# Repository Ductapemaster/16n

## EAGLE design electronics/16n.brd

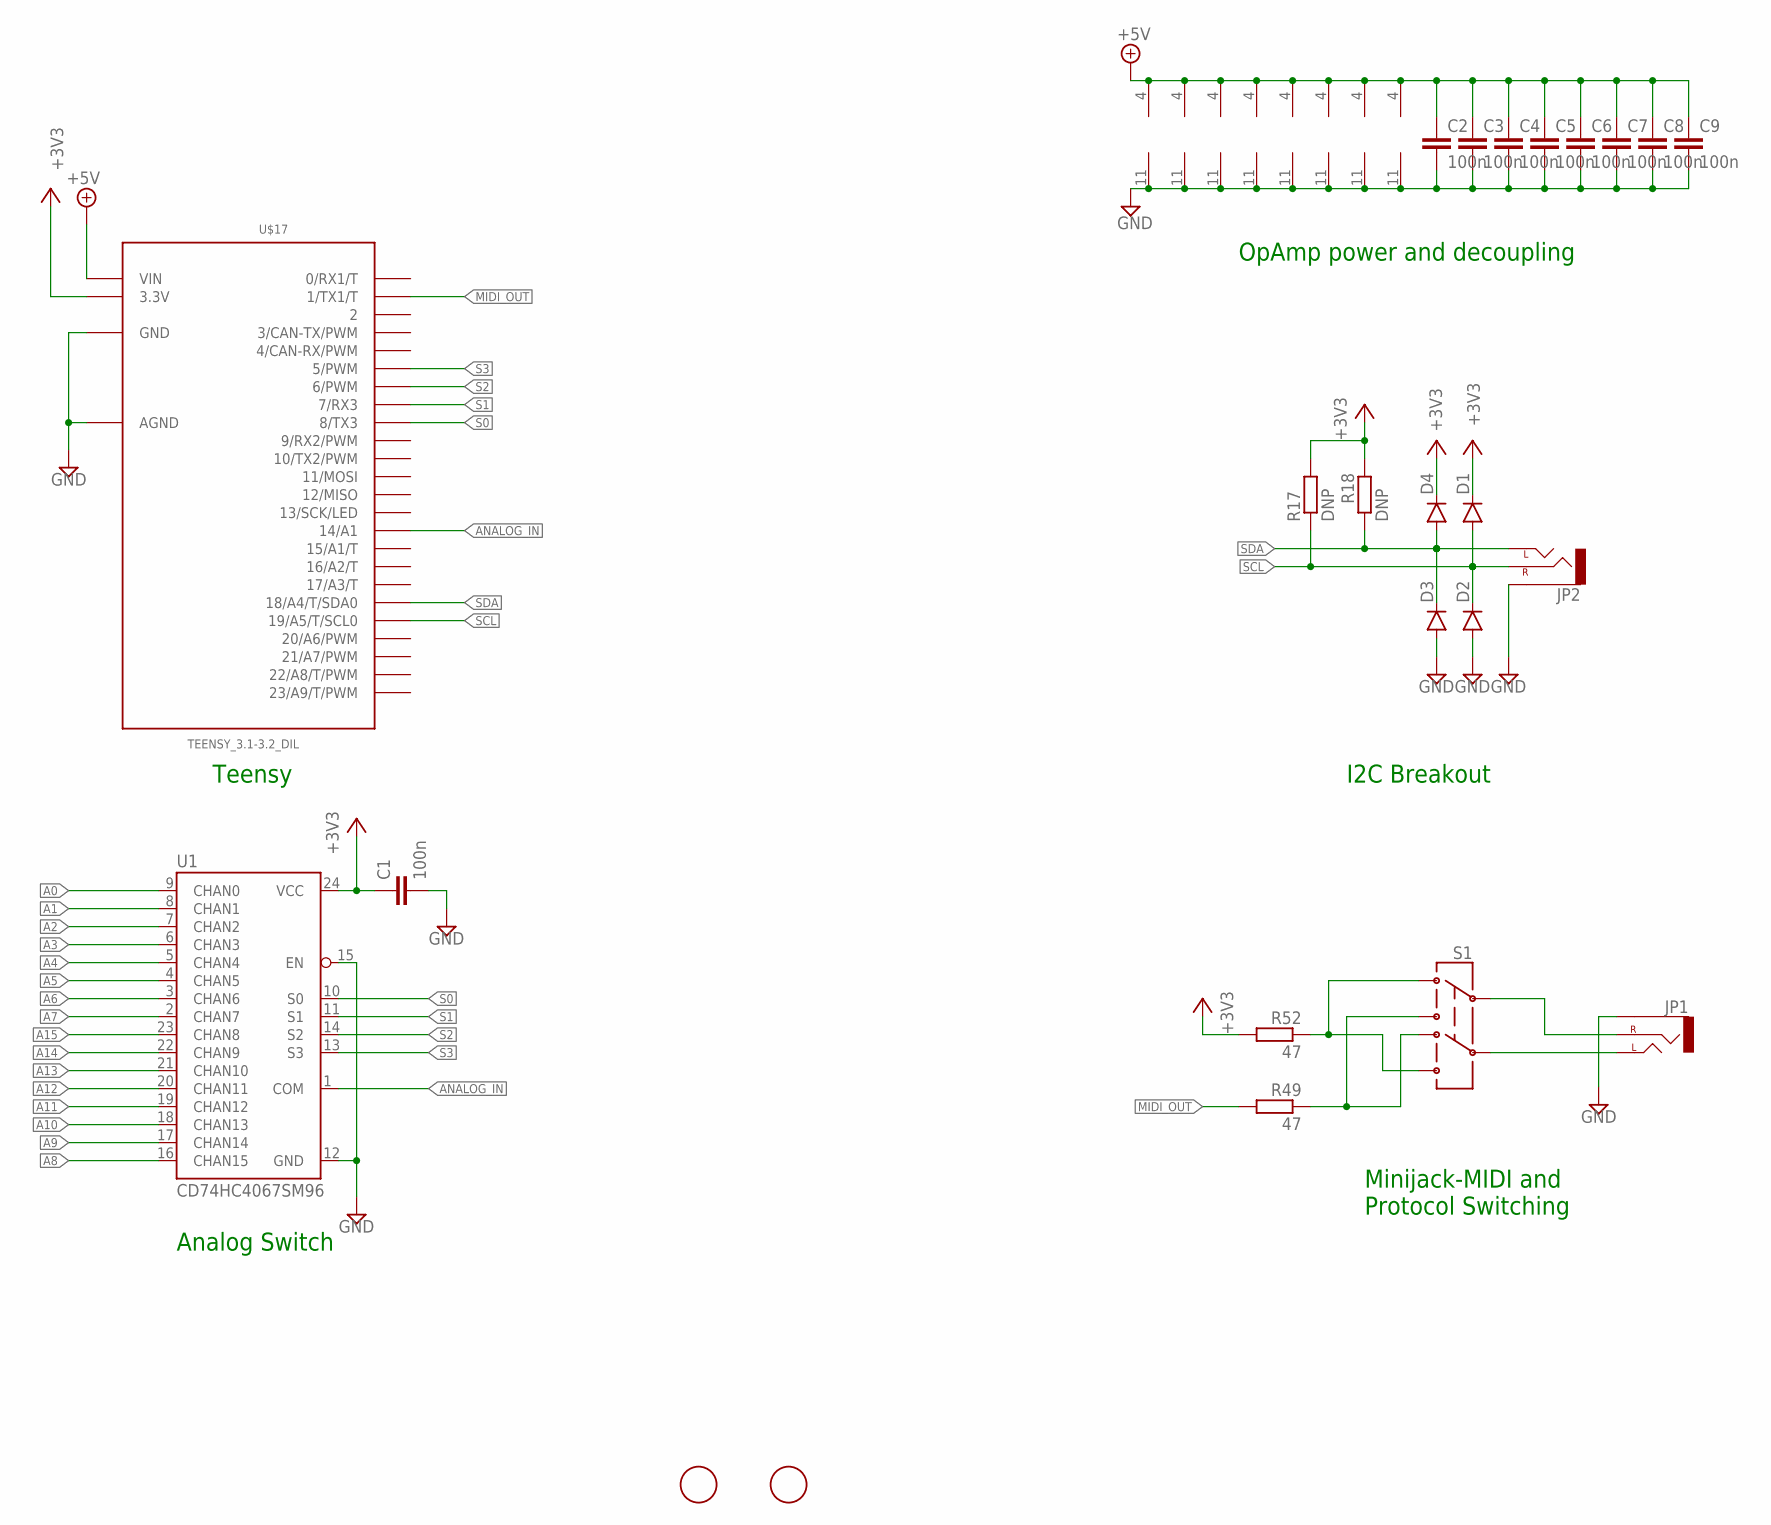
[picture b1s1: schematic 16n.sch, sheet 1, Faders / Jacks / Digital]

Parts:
C1, C2, C3, C4, C5, C6, C7, C8, C9: 100n; C0805
D1, D2, D3, D4: DIODESOD123; SOD-123
FID1, FID2: FIDUCIAL; FIDUCIAL_1MM
JP1, JP2: AUDIO-JACKPTH; AUDIO-JACK
R17, R18: DNP; R0805
R49, R52: 47; R0805
S1: SWITCH-DPDTEG2211; EG2211
U1: CD74HC4067SM96; SOIC127P1030X265-24
U2, U3, U4, U5, U6, U7, U8: MCP6004_SMD; SO14
U9: MCP6004; SO14
U$17: TEENSY_3.1-3.2_DIL; TEENSY_3.0-3.2&LC_DIL

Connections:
+3V3: C1.1, D1.C, D4.C, R17.2, R18.2, R52.2, U1.24 (VCC), U$17.3.3V
+5V: C2.1, C3.1, C4.1, C5.1, C6.1, C7.1, C8.1, C9.1, U2.4 (V+), U3.4 (V+), U4.4 (V+), U5.4 (V+), U6.4 (V+), U7.4 (V+), U8.4 (V+), U9.4 (V+), U$17.VIN; also elsewhere on the board
A0: U1.9 (CHAN0); also elsewhere on the board
A1: U1.8 (CHAN1); also elsewhere on the board
A2: U1.7 (CHAN2); also elsewhere on the board
A3: U1.6 (CHAN3); also elsewhere on the board
A4: U1.5 (CHAN4); also elsewhere on the board
A5: U1.4 (CHAN5); also elsewhere on the board
A6: U1.3 (CHAN6); also elsewhere on the board
A7: U1.2 (CHAN7); also elsewhere on the board
A8: U1.16 (CHAN15); also elsewhere on the board
A9: U1.17 (CHAN14); also elsewhere on the board
A10: U1.18 (CHAN13); also elsewhere on the board
A11: U1.19 (CHAN12); also elsewhere on the board
A12: U1.20 (CHAN11); also elsewhere on the board
A13: U1.21 (CHAN10); also elsewhere on the board
A14: U1.22 (CHAN9); also elsewhere on the board
A15: U1.23 (CHAN8); also elsewhere on the board
ANALOG_IN: U1.1 (COM), U$17.14/A0 (14/A1)
GND: C1.2, C2.2, C3.2, C4.2, C5.2, C6.2, C7.2, C8.2, C9.2, D2.A, D3.A, JP1.SLEEVE, JP2.SLEEVE, U1.12 (GND), U1.15 (EN), U2.11 (V-), U3.11 (V-), U4.11 (V-), U5.11 (V-), U6.11 (V-), U7.11 (V-), U8.11 (V-), U9.11 (V-), U$17.AGND, U$17.GND; also elsewhere on the board
MIDI_OUT: R49.2, U$17.1 (1/TX1/T)
unnamed: JP1.TIP (LEFT), S1.P2 (5)
unnamed: JP1.RING (RIGHT), S1.P1 (2)
unnamed: R49.1, S1.P1-TB (3), S1.P2-TA (4)
unnamed: R52.1, S1.P1-TA (1), S1.P2-TB (6)
S0: U1.10 (S0), U$17.8 (8/TX3)
S1: U1.11 (S1), U$17.7 (7/RX3)
S2: U1.14 (S2), U$17.6 (6/PWM)
S3: U1.13 (S3), U$17.5 (5/PWM)
SCL: D1.A, D2.C, JP2.RING (RIGHT), R17.1, U$17.19/A5 (19/A5/T/SCL0)
SDA: D3.C, D4.A, JP2.TIP (LEFT), R18.1, U$17.18/A4 (18/A4/T/SDA0)

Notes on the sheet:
Teensy
Minijack-MIDI and Protocol Switching
I2C Breakout
OpAmp power and decoupling
Analog Switch

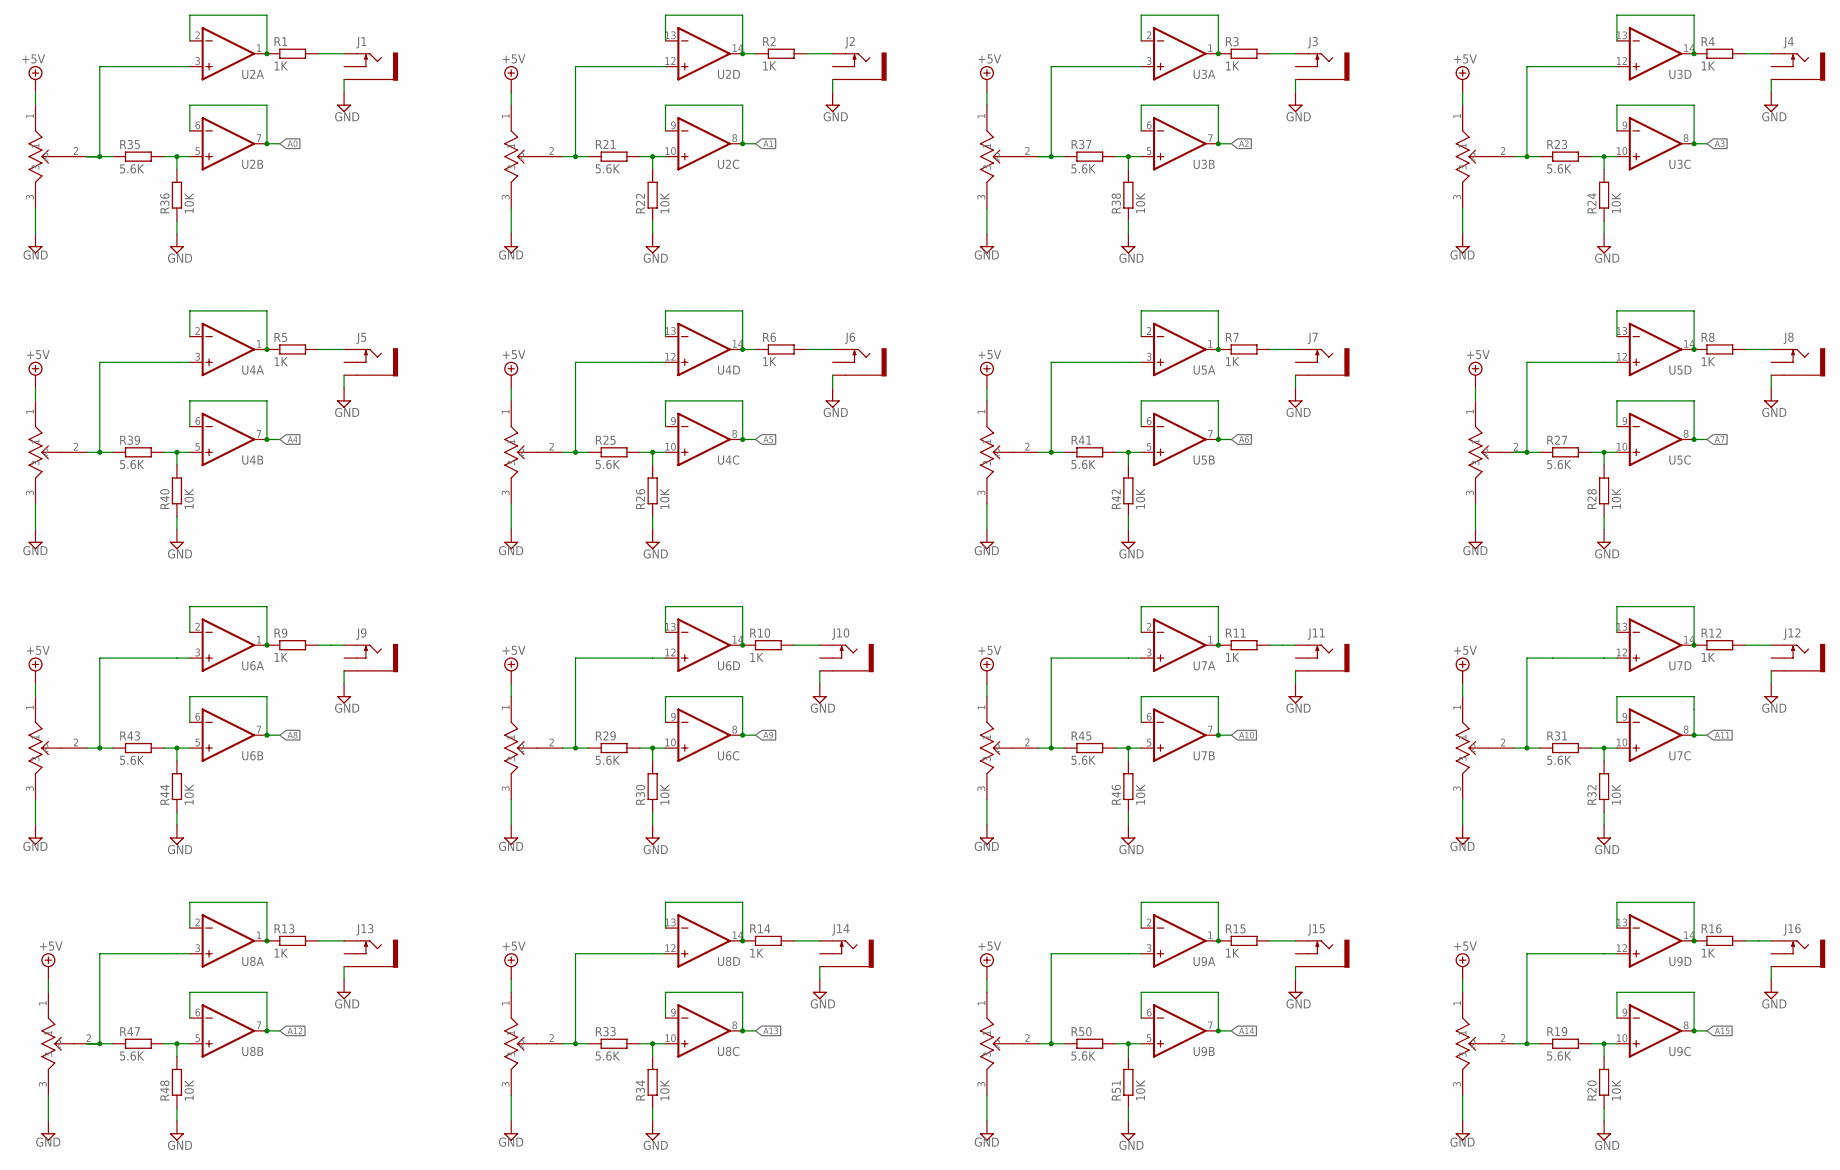
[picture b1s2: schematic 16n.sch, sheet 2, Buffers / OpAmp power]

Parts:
J1, J2, J3, J4, J5, J6, J7, J8, J9, J10, J11, J12, J13, J14, J15, J16: PJ302M
R1, R2, R3, R4, R5, R6, R7, R8, R9, R10, R11, R12, R13, R14, R15, R16: 1K; R0805
R19, R21, R23, R25, R27, R29, R31, R33, R35, R37, R39, R41, R43, R45, R47, R50: 5.6K; R0805
R20, R22, R24, R26, R28, R30, R32, R34, R36, R38, R40, R42, R44, R46, R48, R51: 10K; R0805
U2, U3, U4, U5, U6, U7, U8: MCP6004_SMD; SO14
U9: MCP6004; SO14
U$1, U$2, U$3, U$4, U$5, U$6, U$7, U$8, U$9, U$10, U$11, U$12, U$13, U$14, U$15, U$16: SLIDEPOT-ALPS-60MM; RS6011SP600

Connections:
+5V: U$1.1, U$2.1, U$3.1, U$4.1, U$5.1, U$6.1, U$7.1, U$8.1, U$9.1, U$10.1, U$11.1, U$12.1, U$13.1, U$14.1, U$15.1, U$16.1; also elsewhere on the board
A0: U2.6 (-IN), U2.7 (OUT); also elsewhere on the board
A1: U2.8 (OUT), U2.9 (-IN); also elsewhere on the board
A2: U3.6 (-IN), U3.7 (OUT); also elsewhere on the board
A3: U3.8 (OUT), U3.9 (-IN); also elsewhere on the board
A4: U4.6 (-IN), U4.7 (OUT); also elsewhere on the board
A5: U4.8 (OUT), U4.9 (-IN); also elsewhere on the board
A6: U5.6 (-IN), U5.7 (OUT); also elsewhere on the board
A7: U5.8 (OUT), U5.9 (-IN); also elsewhere on the board
A8: U6.6 (-IN), U6.7 (OUT); also elsewhere on the board
A9: U6.8 (OUT), U6.9 (-IN); also elsewhere on the board
A10: U7.6 (-IN), U7.7 (OUT); also elsewhere on the board
A11: U7.8 (OUT), U7.9 (-IN); also elsewhere on the board
A12: U8.6 (-IN), U8.7 (OUT); also elsewhere on the board
A13: U8.8 (OUT), U8.9 (-IN); also elsewhere on the board
A14: U9.6 (-IN), U9.7 (OUT); also elsewhere on the board
A15: U9.8 (OUT), U9.9 (-IN); also elsewhere on the board
CV1: J1.TIP, R1.2
CV2: J2.TIP, R2.2
CV3: J3.TIP, R3.2
CV4: J4.TIP, R4.2
CV5: J5.TIP, R5.2
CV6: J6.TIP, R6.2
CV7: J7.TIP, R7.2
CV8: J8.TIP, R8.2
CV9: J9.TIP, R9.2
CV10: J10.TIP, R10.2
CV11: J11.TIP, R11.2
CV12: J12.TIP, R12.2
CV13: J13.TIP, R13.2
CV14: J14.TIP, R14.2
CV15: J15.TIP, R15.2
CV16: J16.TIP, R16.2
GND: J1.GND (SLEEVE), J2.GND (SLEEVE), J3.GND (SLEEVE), J4.GND (SLEEVE), J5.GND (SLEEVE), J6.GND (SLEEVE), J7.GND (SLEEVE), J8.GND (SLEEVE), J9.GND (SLEEVE), J10.GND (SLEEVE), J11.GND (SLEEVE), J12.GND (SLEEVE), J13.GND (SLEEVE), J14.GND (SLEEVE), J15.GND (SLEEVE), J16.GND (SLEEVE), R20.1, R22.1, R24.1, R26.1, R28.1, R30.1, R32.1, R34.1, R36.1, R38.1, R40.1, R42.1, R44.1, R46.1, R48.1, R51.1, U$1.3, U$2.3, U$3.3, U$4.3, U$5.3, U$6.3, U$7.3, U$8.3, U$9.3, U$10.3, U$11.3, U$12.3, U$13.3, U$14.3, U$15.3, U$16.3; also elsewhere on the board
unnamed: R37.2, R38.2, U3.5 (+IN)
unnamed: R23.2, R24.2, U3.10 (+IN)
unnamed: R39.2, R40.2, U4.5 (+IN)
unnamed: R25.2, R26.2, U4.10 (+IN)
unnamed: R35.2, R36.2, U2.5 (+IN)
unnamed: R21.2, R22.2, U2.10 (+IN)
unnamed: R41.2, R42.2, U5.5 (+IN)
unnamed: R27.2, R28.2, U5.10 (+IN)
unnamed: R43.2, R44.2, U6.5 (+IN)
unnamed: R29.2, R30.2, U6.10 (+IN)
unnamed: R45.2, R46.2, U7.5 (+IN)
unnamed: R19.2, R20.2, U9.10 (+IN)
unnamed: R50.2, R51.2, U9.5 (+IN)
unnamed: R33.2, R34.2, U8.10 (+IN)
unnamed: R47.2, R48.2, U8.5 (+IN)
unnamed: R31.2, R32.2, U7.10 (+IN)
unnamed: R1.1, U2.1 (OUT), U2.2 (-IN)
unnamed: R2.1, U2.13 (-IN), U2.14 (OUT)
unnamed: R3.1, U3.1 (OUT), U3.2 (-IN)
unnamed: R4.1, U3.13 (-IN), U3.14 (OUT)
unnamed: R5.1, U4.1 (OUT), U4.2 (-IN)
unnamed: R6.1, U4.13 (-IN), U4.14 (OUT)
unnamed: R7.1, U5.1 (OUT), U5.2 (-IN)
unnamed: R8.1, U5.13 (-IN), U5.14 (OUT)
unnamed: R9.1, U6.1 (OUT), U6.2 (-IN)
unnamed: R10.1, U6.13 (-IN), U6.14 (OUT)
unnamed: R11.1, U7.1 (OUT), U7.2 (-IN)
unnamed: R12.1, U7.13 (-IN), U7.14 (OUT)
unnamed: R13.1, U8.1 (OUT), U8.2 (-IN)
unnamed: R14.1, U8.13 (-IN), U8.14 (OUT)
unnamed: R15.1, U9.1 (OUT), U9.2 (-IN)
unnamed: R16.1, U9.13 (-IN), U9.14 (OUT)
W0: R35.1, U2.3 (+IN), U$1.2
W1: R21.1, U2.12 (+IN), U$2.2
W2: R37.1, U3.3 (+IN), U$3.2
W3: R23.1, U3.12 (+IN), U$4.2
W4: R39.1, U4.3 (+IN), U$5.2
W5: R25.1, U4.12 (+IN), U$6.2
W6: R41.1, U5.3 (+IN), U$7.2
W7: R27.1, U5.12 (+IN), U$8.2
W8: R43.1, U6.3 (+IN), U$9.2
W9: R29.1, U6.12 (+IN), U$10.2
W10: R45.1, U7.3 (+IN), U$11.2
W11: R31.1, U7.12 (+IN), U$12.2
W12: R47.1, U8.3 (+IN), U$13.2
W13: R33.1, U8.12 (+IN), U$14.2
W14: R50.1, U9.3 (+IN), U$15.2
W15: R19.1, U9.12 (+IN), U$16.2

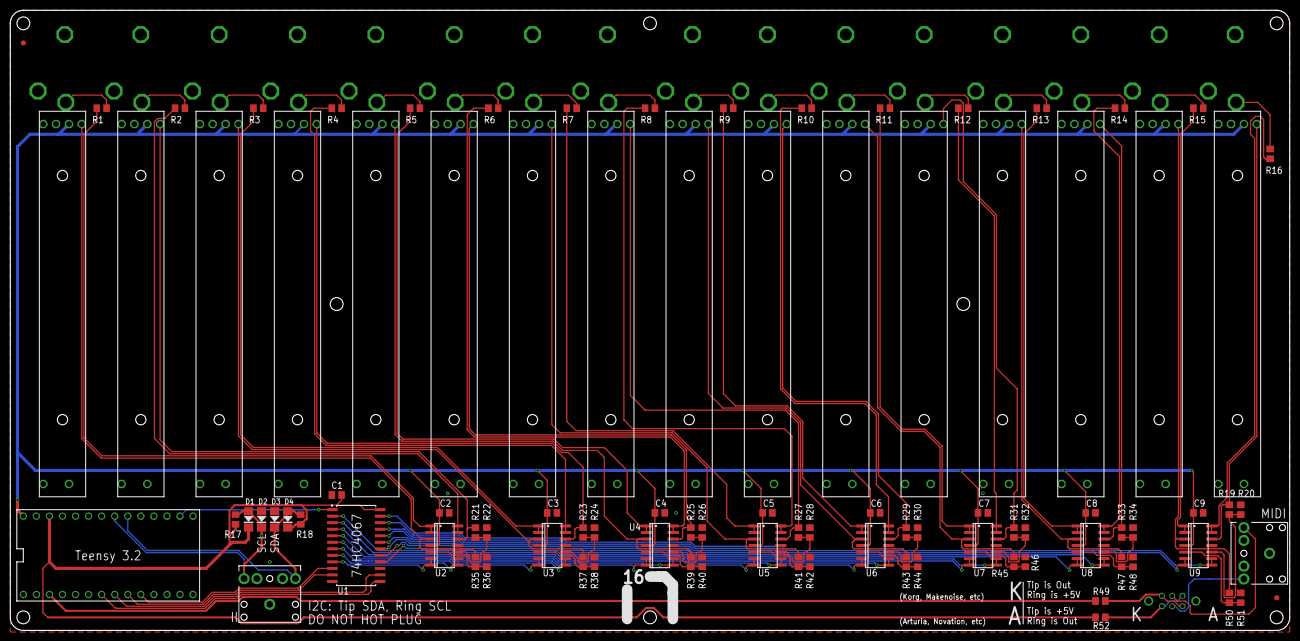
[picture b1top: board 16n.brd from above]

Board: 2 copper layers, 248.9 x 120.7 mm, 112 parts (0 on the bottom side), 95 nets.

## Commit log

2019-08-08 Organize opamp page. General cleanup.
    Move wipers and CV jacks to 2nd page and lay out in a clearer way. Add frames that work with cross reference symbols.
2019-08-08 Organize first page of schematic
    Moved things around, made net labels and supply symbols consistent, add labels

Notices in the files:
electronics/16n.brd:
CC-BY-SA 4.0
Creative Commons
Attribution / ShareAlike
parts and their libraries:
SparkFun-Connectors: Licensing: Creative Commons ShareAlike 4.0 International - https://creativecommons.org/licenses/by-sa/4.0
